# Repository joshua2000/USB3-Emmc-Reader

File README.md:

# USB3-Emmc-Reader
* Version 1.0 of an Emmc Reader 
* A picked up project from @*[dvdfreitag](https://github.com/dvdfreitag/USB3-eMMC)* . 
* There are a few modifications done, such as addition of VDD power on pin 21 and 20.
* Front Pcb image:

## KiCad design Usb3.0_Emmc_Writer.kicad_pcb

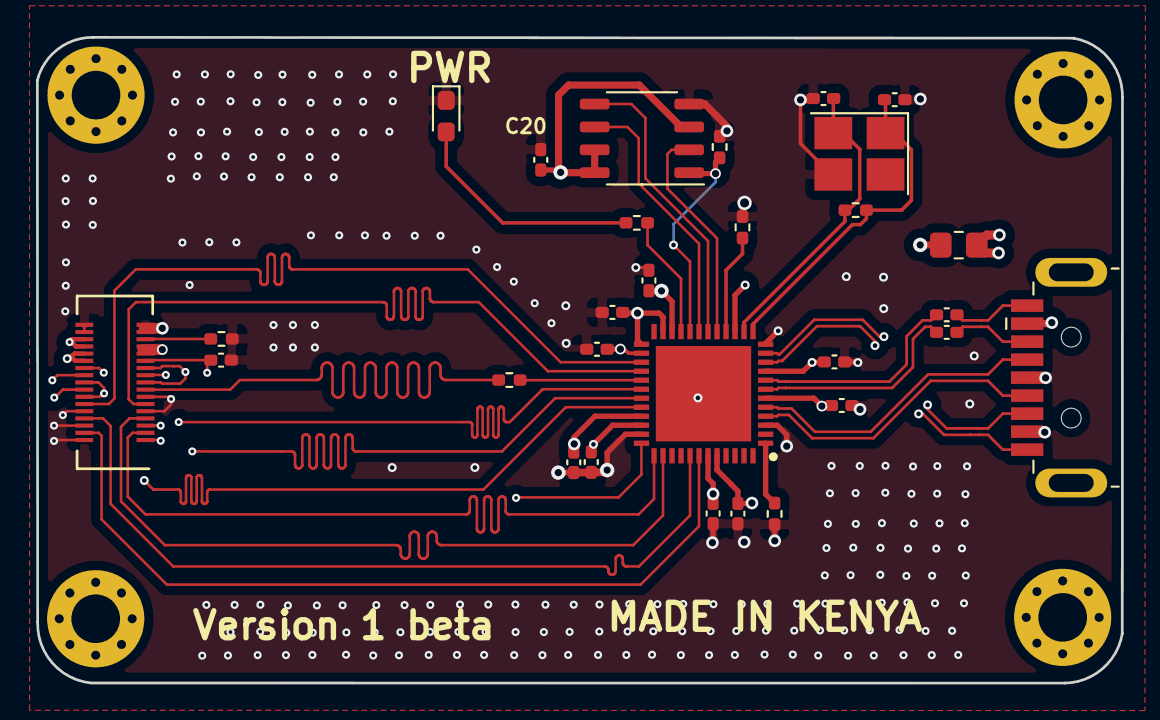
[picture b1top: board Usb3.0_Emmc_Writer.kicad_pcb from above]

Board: 4 copper layers, 60.3 x 35.9 mm, 33 parts (0 on the bottom side), 37 nets.

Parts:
C1, C7: 1uF; C_0402_1005Metric_Pad0.74x0.62mm_HandSolder
C2, C3, C4, C5, C6, C10, C18, C19: 0.1uF; C_0402_1005Metric_Pad0.74x0.62mm_HandSolder
C14: 2.2uF; C_0402_1005Metric_Pad0.74x0.62mm_HandSolder
C15, C16, C17, C20: 10pF; C_0402_1005Metric_Pad0.74x0.62mm_HandSolder
D1: LED; LED_0603_1608Metric_Pad1.05x0.95mm_HandSolder
H1, H1#2, H2, H2#2: MountingHole; MountingHole_2.7mm_Pad_Via
IC1: GL3224-ONYXX; QFN50P700X700X80-49N
J1: USB3_B; USB3_A_Plug_Wuerth_692112030100_Horizontal
R1: 32.7M; R_0402_1005Metric_Pad0.72x0.64mm_HandSolder
R2: 10K; R_0402_1005Metric_Pad0.72x0.64mm_HandSolder
R3: 0M; R_0402_1005Metric_Pad0.72x0.64mm_HandSolder
R4: 10kΩ; R_0402_1005Metric_Pad0.72x0.64mm_HandSolder
R6: 1M; R_0402_1005Metric_Pad0.72x0.64mm_HandSolder
R7: 680M; R_0402_1005Metric_Pad0.72x0.64mm_HandSolder
R9: 500M; R_0805_2012Metric_Pad1.20x1.40mm_HandSolder
R10: 32.7m; R_0402_1005Metric_Pad0.72x0.64mm_HandSolder
U1: GB042-34S-H10
U2: MX25L512EMI-10G; SOP-8_3.9x4.9mm_P1.27mm
Y1: 25Mhz; Crystal_SMD_3225-4Pin_3.2x2.5mm_HandSoldering

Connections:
+1.2V: C6.1, C10.1, IC1.9, IC1.26
AVDD33: C1.1, C3.1, C5.1, C15.2, C20.1, IC1.6, IC1.15, IC1.23, IC1.25, IC1.34, IC1.44, U1.22, U1.23, U2.3, U2.7, U2.8
CLK: R1.1, U1.8
CMD: IC1.30, U1.25
CS: IC1.20, R4.1, U2.1
D0: IC1.28, U1.6
D1: IC1.27, U1.29
D2: IC1.32, U1.27
D3: IC1.31, U1.10
D4: IC1.38, U1.4
D5: IC1.37, U1.2
D6: IC1.42, U1.33
D7: IC1.41, U1.31
D+: IC1.5, J1.2
D-: IC1.4, J1.3
GND: C1.2, C2.1, C3.2, C4.1, C5.2, C6.2, C7.2, C10.2, C14.2, C15.1, C16.2, C17.2, C20.2, D1.1, IC1.3, IC1.12, IC1.35, IC1.49, J1.4, J1.7, R2.2, R3.1, R4.2, R7.2, U1.1, U1.3, U1.5, U1.7, U1.9, U1.11, U1.13, U1.14, U1.16, U1.17, U1.18, U1.19, U1.24, U1.26, U1.28, U1.30, U1.32, U1.34, U2.4, Y1.3
MISO_101: IC1.17, U2.2
MOSI_100: IC1.18, U2.5
unnamed: C16.1, IC1.14, R6.1, Y1.2
unnamed: C17.1, IC1.13, R6.2, Y1.1
unnamed: D1.2, R10.2
unnamed: IC1.1, R3.2
unnamed: IC1.16, R7.1
unnamed: IC1.21, R10.1
unnamed: IC1.29, R1.2
unnamed: J1.1, R9.1
unnamed: R2.1, U1.15
RST: C7.1, IC1.36, U1.12
SCK: IC1.19, U2.6
SD_VDD: C2.2, C4.2, IC1.33, IC1.43, U1.20, U1.21
SSRX+: C19.1, J1.9
SSRX-: C18.1, J1.8
SSTX+: IC1.11, J1.6
SSTX-: IC1.10, J1.5
TX+: C19.2, IC1.8
TX-: C18.2, IC1.7
vbus: C14.1, IC1.22, R9.2

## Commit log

2021-06-14 V1 Commit
    There are a few errors that need changing:
    1. Linking the Kicad library files
    2. Making the bus length shorter < 4cm.
    3. More newbie mistakes need correcting
2021-06-14 Updating Read.me
    comments update
2021-06-14 Add files via upload
    Images of the board
